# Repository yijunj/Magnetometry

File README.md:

# Magnetometry
Hogan Lab tower magnetometry project. Please see the PDF documentation for details.

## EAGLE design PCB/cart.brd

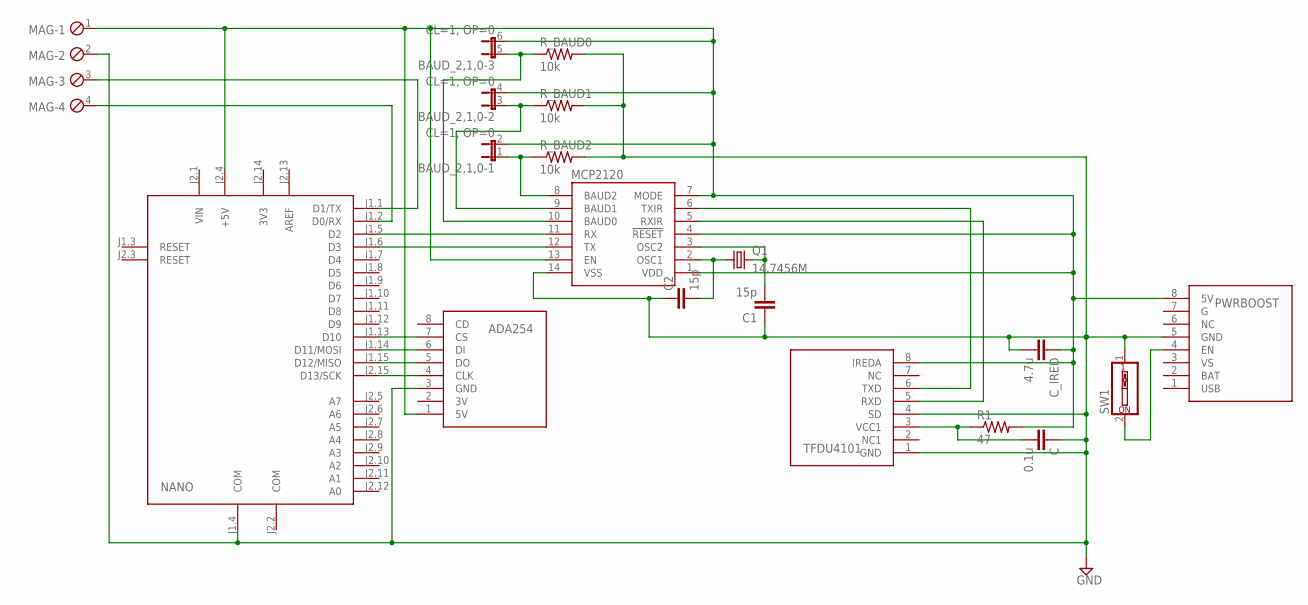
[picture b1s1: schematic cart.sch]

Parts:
ADA254: ADA254_SD_READER
BAUD_2,1,0: CL=1, OP=0; JP3Q
C: 0.1u; C1206
C1, C2: 15p; C1206
C_IRED: 4.7u; C1206
MAG: MPT4; 4POL254
MCP2120: MCP2120_SOIC; SO14
NANO: ARDUINO_NANO2
PWRBOOST: POWERBOOST_1000C
Q1: 14.7456M; TC26V
R1: 47; R1206W
R_BAUD0, R_BAUD1, R_BAUD2: 10k; R1206W
SW1: SW_DIP-1; EDG-01
TFDU4101: TFDU4101_SIDE

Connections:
3V3: NANO.J2.14 (3V3)
AREF: NANO.J2.13 (AREF)
COM: NANO.J2.2 (COM)
GND: ADA254.3 (GND), C.1, C1.1, C2.1, C_IRED.2, MAG.2, MCP2120.14 (VSS), NANO.J1.4 (COM), PWRBOOST.5 (GND), R_BAUD0.2, R_BAUD1.2, R_BAUD2.2, SW1.1, TFDU4101.1 (GND), TFDU4101.4 (SD)
unnamed: MCP2120.11 (RX), NANO.J1.5 (D2)
unnamed: C2.2, MCP2120.2 (OSC1), Q1.1
unnamed: ADA254.1 (5V), BAUD_2,1,0.2, BAUD_2,1,0.4 (2), BAUD_2,1,0.6 (2), C_IRED.1, MAG.1, MCP2120.1 (VDD), MCP2120.4 (!RESET), MCP2120.7 (MODE), MCP2120.13 (EN), NANO.J2.4 (+5V), PWRBOOST.8 (5V), R1.2, TFDU4101.8 (IREDA)
unnamed: MCP2120.12 (TX), NANO.J1.6 (D3)
unnamed: BAUD_2,1,0.5 (1), MCP2120.10 (BAUD0), R_BAUD0.1
unnamed: BAUD_2,1,0.3 (1), MCP2120.9 (BAUD1), R_BAUD1.1
unnamed: BAUD_2,1,0.1, MCP2120.8 (BAUD2), R_BAUD2.1
unnamed: ADA254.4 (CLK), NANO.J2.15 (D13/SCK)
unnamed: C1.2, MCP2120.3 (OSC2), Q1.2
unnamed: MCP2120.6 (TXIR), TFDU4101.6 (TXD)
unnamed: MCP2120.5 (RXIR), TFDU4101.5 (RXD)
unnamed: ADA254.5 (DO), NANO.J1.15 (D12/MISO)
unnamed: PWRBOOST.4 (EN), SW1.2
unnamed: C.2, R1.1, TFDU4101.3 (VCC1)
unnamed: ADA254.6 (DI), NANO.J1.14 (D11/MOSI)
unnamed: ADA254.7 (CS), NANO.J1.13 (D10)
unnamed: MAG.3, NANO.J1.1 (D1/TX)
unnamed: MAG.4, NANO.J1.2 (D0/RX)
VIN: NANO.J2.1 (VIN)

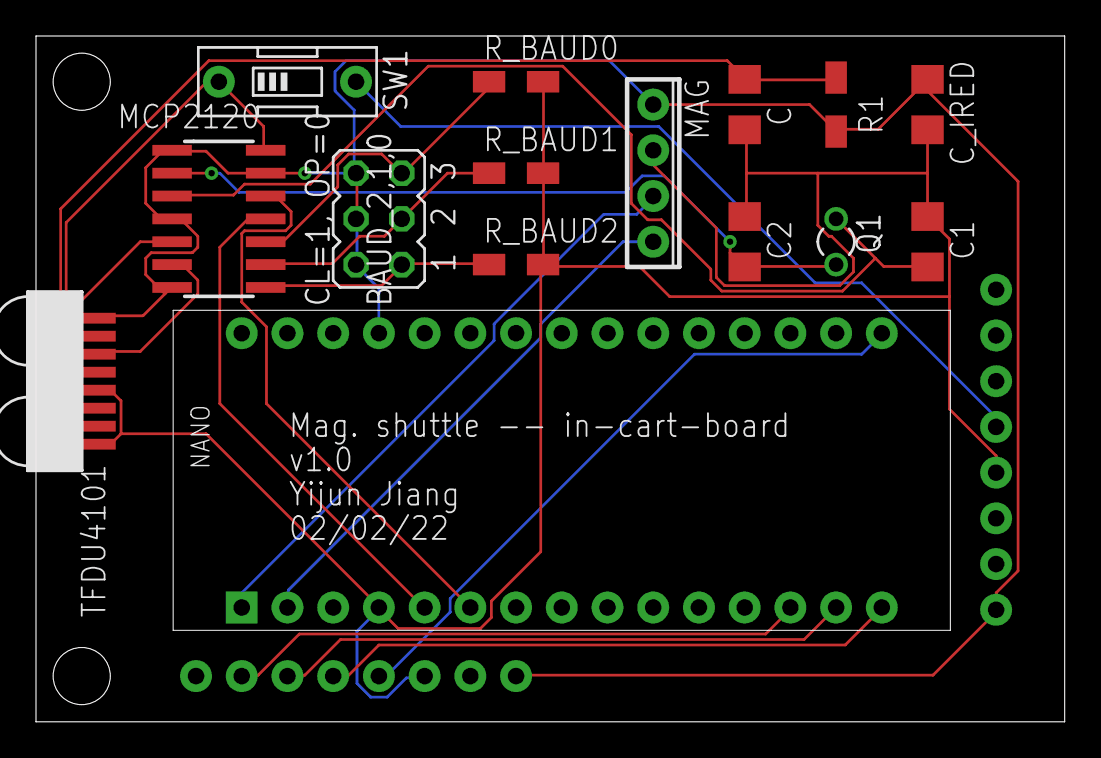
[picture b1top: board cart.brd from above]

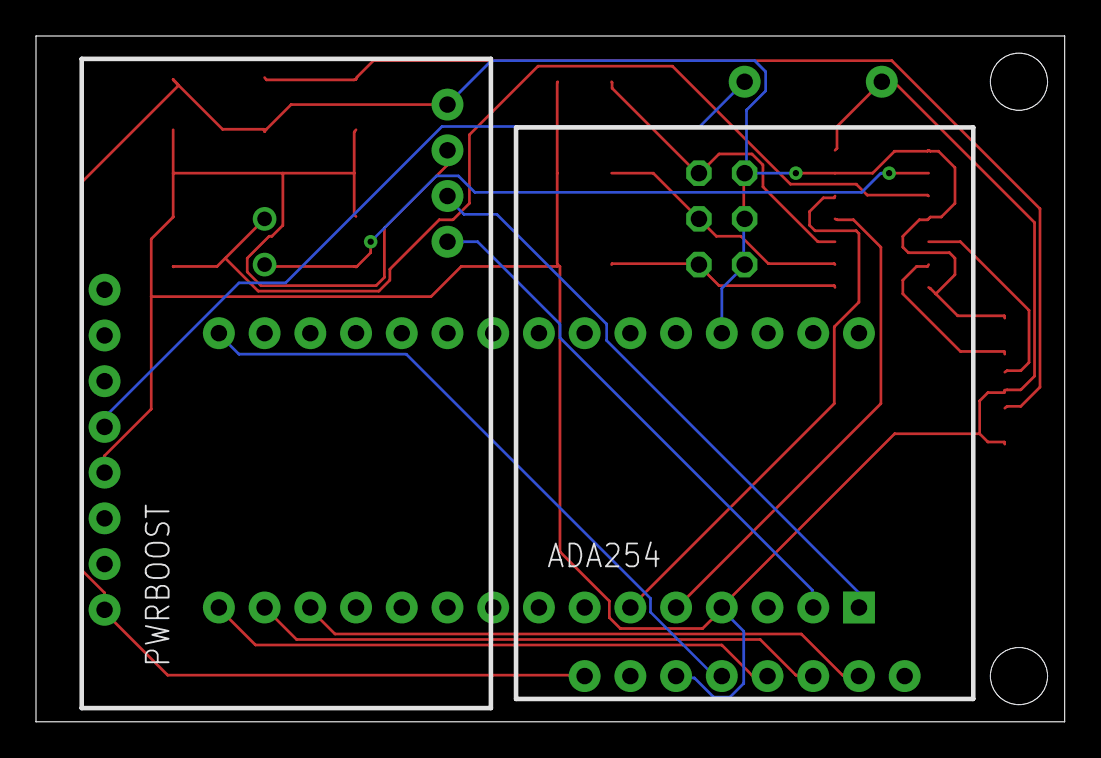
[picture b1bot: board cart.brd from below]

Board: 2 copper layers, 57.1 x 38.1 mm, 17 parts (2 on the bottom side), 19 nets.

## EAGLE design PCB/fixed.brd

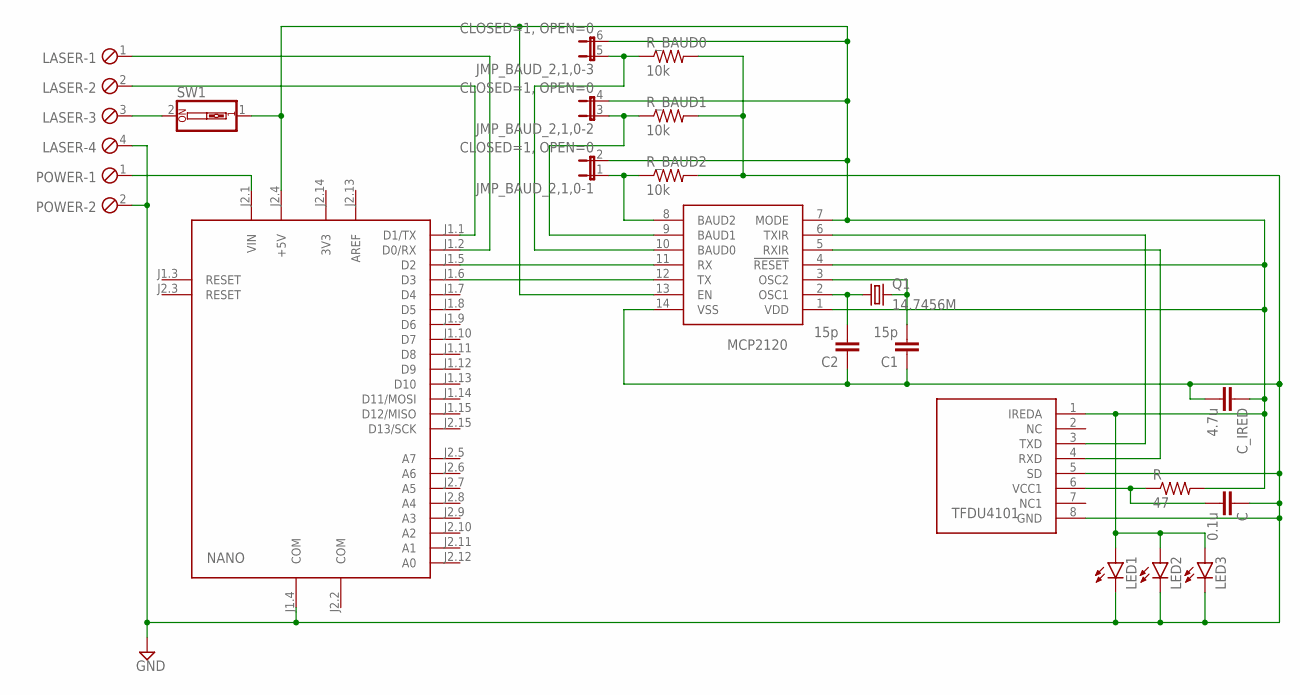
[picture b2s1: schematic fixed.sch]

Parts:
C: 0.1u; C1206
C1, C2: 15p; C1206
C_IRED: 4.7u; C1206
JMP_BAUD_2,1,0: CLOSED=1, OPEN=0; JP3Q
LASER: MPT4; 4POL254
LED1, LED2, LED3: LED5MM
MCP2120: MCP2120_SOIC; SO14
NANO: ARDUINO_NANO2
POWER: MPT2; 2POL254
Q1: 14.7456M; TC26V
R: 47; R1206W
R_BAUD0, R_BAUD1, R_BAUD2: 10k; R1206W
SW1: SW_DIP-1; EDG-01
TFDU4101: TFDU4101_TOP

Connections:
3V3: NANO.J2.14 (3V3)
AREF: NANO.J2.13 (AREF)
COM: NANO.J2.2 (COM)
GND: C.1, C1.1, C2.1, C_IRED.2, LASER.4, LED1.K (C), LED2.K (C), LED3.K (C), MCP2120.14 (VSS), NANO.J1.4 (COM), POWER.2, R_BAUD0.2, R_BAUD1.2, R_BAUD2.2, TFDU4101.5 (SD), TFDU4101.8 (GND)
unnamed: MCP2120.11 (RX), NANO.J1.5 (D2)
unnamed: C2.2, MCP2120.2 (OSC1), Q1.1
unnamed: C_IRED.1, JMP_BAUD_2,1,0.2, JMP_BAUD_2,1,0.4 (2), JMP_BAUD_2,1,0.6 (2), LED1.A, LED2.A, LED3.A, MCP2120.1 (VDD), MCP2120.4 (!RESET), MCP2120.7 (MODE), MCP2120.13 (EN), NANO.J2.4 (+5V), R.2, SW1.1, TFDU4101.1 (IREDA)
unnamed: MCP2120.12 (TX), NANO.J1.6 (D3)
unnamed: JMP_BAUD_2,1,0.5 (1), MCP2120.10 (BAUD0), R_BAUD0.1
unnamed: JMP_BAUD_2,1,0.3 (1), MCP2120.9 (BAUD1), R_BAUD1.1
unnamed: JMP_BAUD_2,1,0.1, MCP2120.8 (BAUD2), R_BAUD2.1
unnamed: LASER.3, SW1.2
unnamed: C1.2, MCP2120.3 (OSC2), Q1.2
unnamed: MCP2120.6 (TXIR), TFDU4101.3 (TXD)
unnamed: MCP2120.5 (RXIR), TFDU4101.4 (RXD)
unnamed: LASER.2, NANO.J1.1 (D1/TX)
unnamed: NANO.J2.1 (VIN), POWER.1
unnamed: C.2, R.1, TFDU4101.6 (VCC1)
unnamed: LASER.1, NANO.J1.2 (D0/RX)

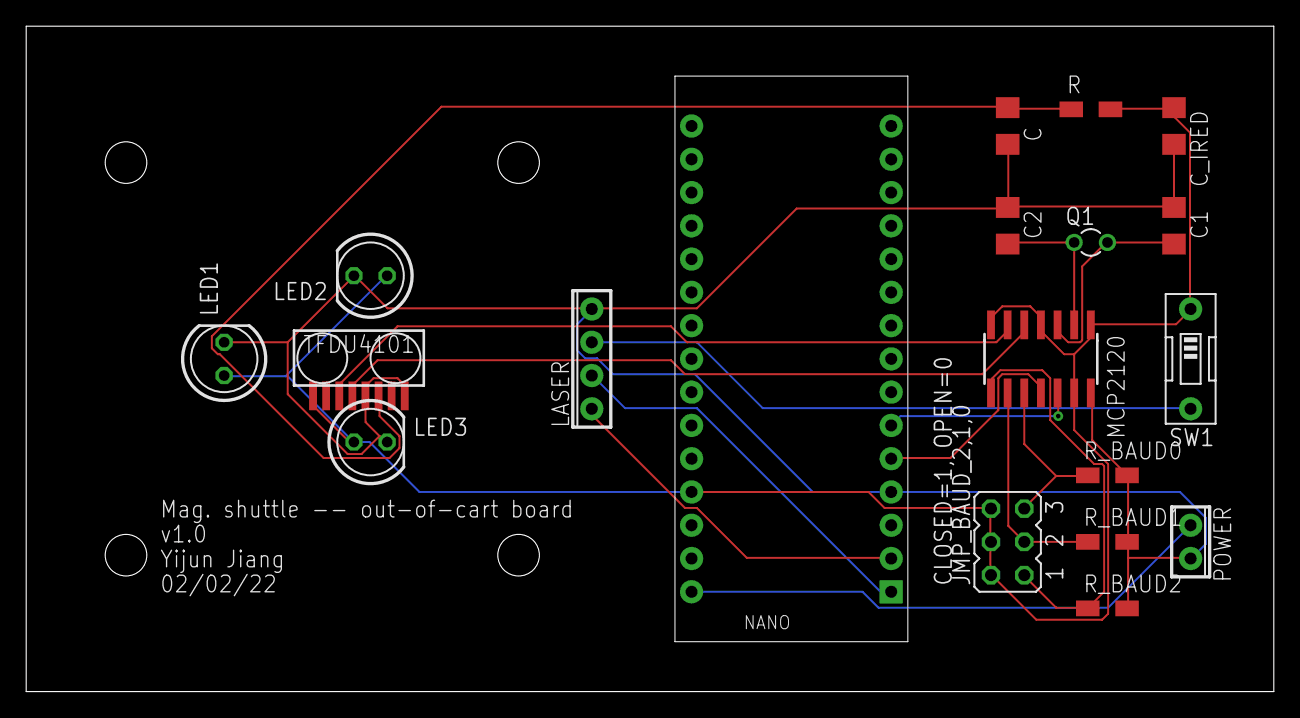
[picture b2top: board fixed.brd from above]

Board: 2 copper layers, 95.2 x 50.8 mm, 19 parts (0 on the bottom side), 16 nets.

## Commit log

2023-07-01 Create test
2023-07-01 Rename PCB/test to test
